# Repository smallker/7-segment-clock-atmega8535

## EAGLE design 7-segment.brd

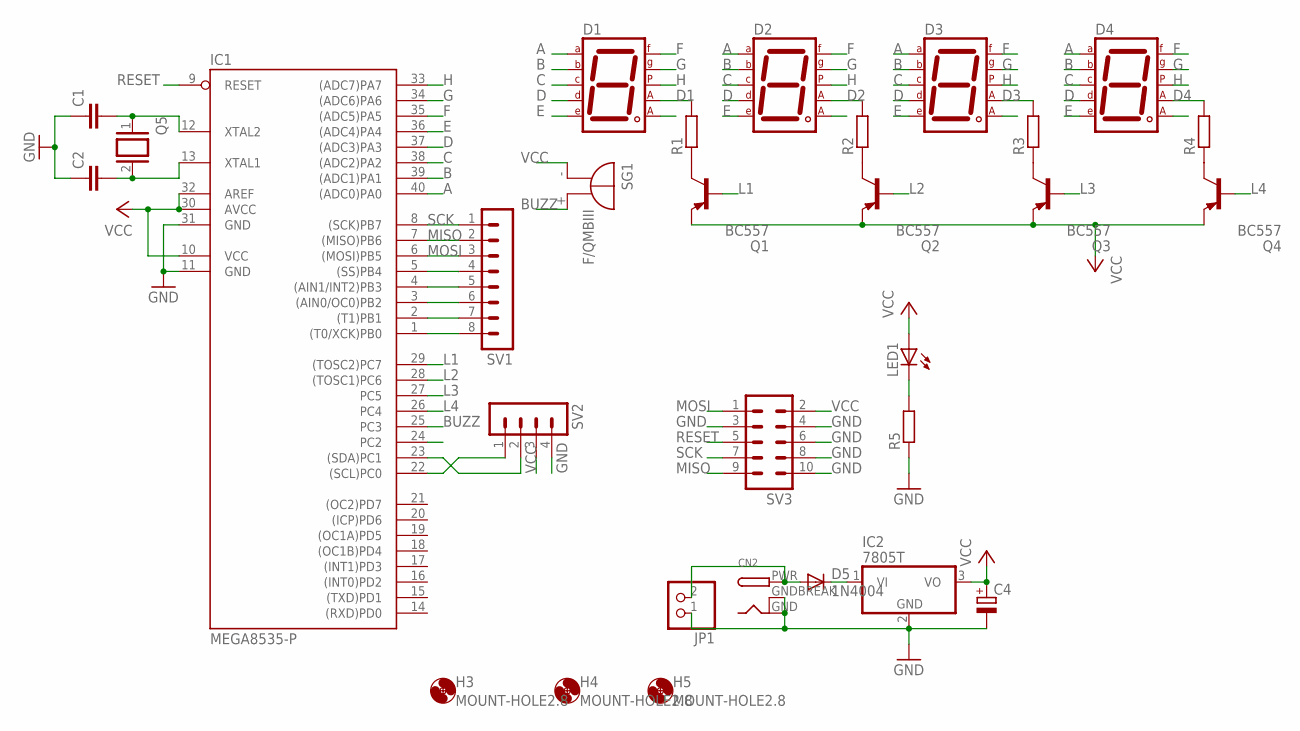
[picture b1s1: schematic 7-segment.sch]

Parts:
C1, C2: C-EU025-024X044; C025-024X044
C4: CPOL-EUE2,5-6E; E2,5-6E
CN2: DCBARRELPTH; DCJACK_2MM_PTH
D1, D2, D3, D4: 7SEG-CA0.8INCH; 7SEG-13
D5: 1N4004; DO41-10
H3, H4, H5: MOUNT-HOLE2.8; 2,8
IC1: MEGA8535-P; DIL40
IC2: 7805T; TO220H
JP1: PINHD-1X2; 1X02
LED1: LED3MM
Q1, Q2, Q3, Q4: BC557; TO92-EBC
Q5: XTAL/S; QS
R1, R2, R3, R4, R5: R-EU_0207/7; 0207/7
SG1: F/QMBIII
SV1: MA08-1
SV2: MA04-1
SV3: MA05-2

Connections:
A: D1.7 (A), D2.7 (A), D3.7 (A), D4.7 (A), IC1.40 ((ADC0)PA0)
B: D1.6 (B), D2.6 (B), D3.6 (B), D4.6 (B), IC1.39 ((ADC1)PA1)
BUZZ: IC1.25 (PC3), SG1.+ (-)
C: D1.4 (C), D2.4 (C), D3.4 (C), D4.4 (C), IC1.38 ((ADC2)PA2)
D: D1.2 (D), D2.2 (D), D3.2 (D), D4.2 (D), IC1.37 ((ADC3)PA3)
D1: D1.3 (CA1), R1.2
D2: D2.3 (CA1), R2.2
D3: D3.3 (CA1), R3.2
D4: D4.3 (CA1), R4.2
E: D1.1 (E), D2.1 (E), D3.1 (E), D4.1 (E), IC1.36 ((ADC4)PA4)
F: D1.9 (F), D2.9 (F), D3.9 (F), D4.9 (F), IC1.35 ((ADC5)PA5)
G: D1.10 (G), D2.10 (G), D3.10 (G), D4.10 (G), IC1.34 ((ADC6)PA6)
GND: C1.1, C2.1, C4.-, CN2.GND, CN2.GNDBREAK, IC1.11 (GND), IC1.31 (GND), IC2.2 (GND), JP1.1, R5.1, SV2.4, SV3.3, SV3.4, SV3.6, SV3.8, SV3.10
H: D1.5 (DP), D2.5 (DP), D3.5 (DP), D4.5 (DP), IC1.33 ((ADC7)PA7)
L1: IC1.29 ((TOSC2)PC7), Q1.B
L2: IC1.28 ((TOSC1)PC6), Q2.B
L3: IC1.27 (PC5), Q3.B
L4: IC1.26 (PC4), Q4.B
MISO: IC1.7 ((MISO)PB6), SV1.2, SV3.9
MOSI: IC1.6 ((MOSI)PB5), SV1.3, SV3.1
unnamed: Q1.C, R1.1
unnamed: Q2.C, R2.1
unnamed: Q3.C, R3.1
unnamed: Q4.C, R4.1
unnamed: CN2.PWR, D5.A, JP1.2
unnamed: C1.2, IC1.12 (XTAL2), Q5.1
unnamed: C2.2, IC1.13 (XTAL1), Q5.2
unnamed: D5.C, IC2.1 (VI)
unnamed: IC1.5 ((SS)PB4), SV1.4
unnamed: IC1.4 ((AIN1/INT2)PB3), SV1.5
unnamed: IC1.3 ((AIN0/OC0)PB2), SV1.6
unnamed: IC1.2 ((T1)PB1), SV1.7
unnamed: IC1.1 ((T0/XCK)PB0), SV1.8
unnamed: LED1.K (C), R5.2
unnamed: IC1.23 ((SDA)PC1), SV2.2
unnamed: IC1.22 ((SCL)PC0), SV2.1
RESET: IC1.9 (RESET), SV3.5
SCK: IC1.8 ((SCK)PB7), SV1.1, SV3.7
VCC: C4.+, IC1.10 (VCC), IC1.30 (AVCC), IC1.32 (AREF), IC2.3 (VO), LED1.A, Q1.E, Q2.E, Q3.E, Q4.E, SG1.- (+), SV2.3, SV3.2

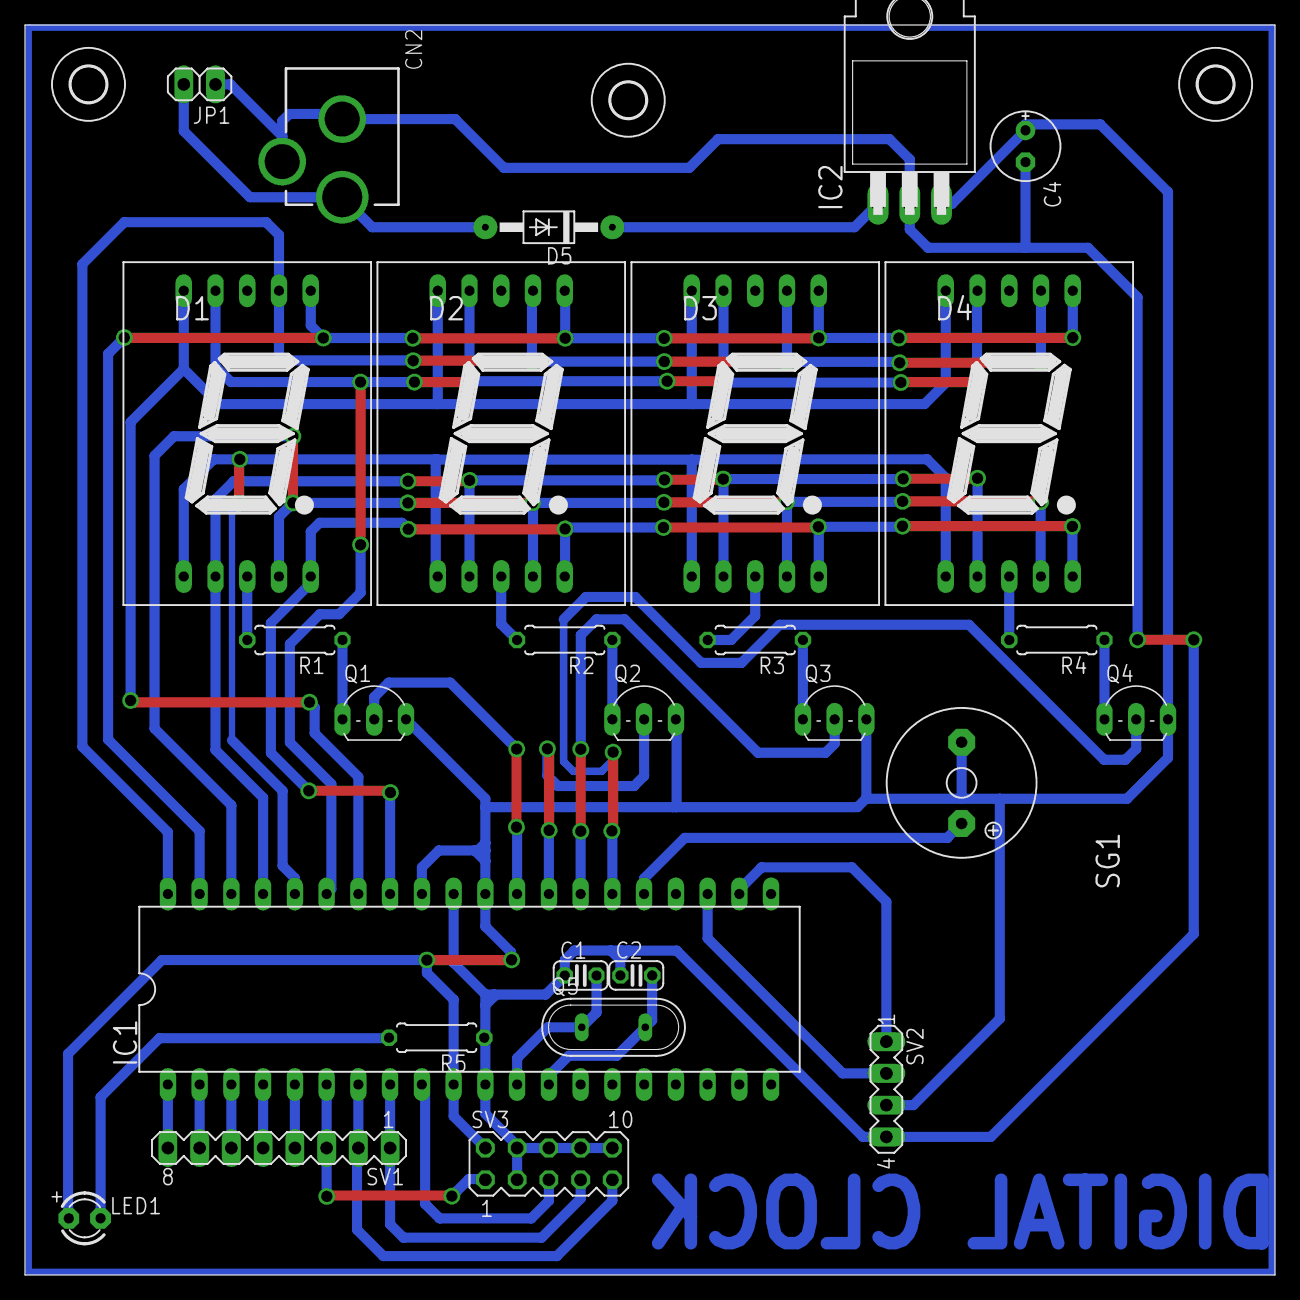
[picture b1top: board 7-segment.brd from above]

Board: 2 copper layers, 100.0 x 100.0 mm, 30 parts (0 on the bottom side), 39 nets.
